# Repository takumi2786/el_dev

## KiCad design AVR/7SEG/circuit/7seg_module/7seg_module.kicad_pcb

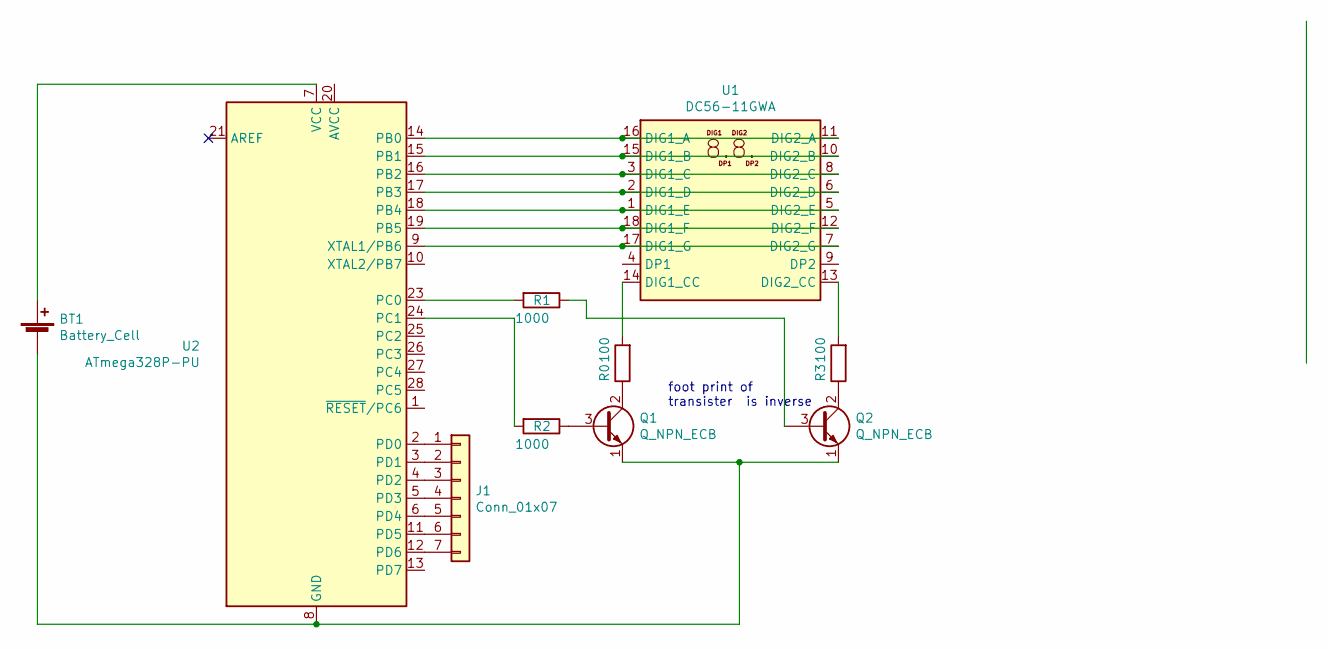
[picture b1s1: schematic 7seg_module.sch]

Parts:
BT1: Battery_Cell; v_dip
J1: Conn_01x07; PinSocket_1x07_P2.54mm_Horizontal
Q1: Q_NPN_ECB; TO-92L_Inline
Q2: Q_NPN_ECB; TO-92_Inline
R0, R3: 100; R_Axial_DIN0309_L9.0mm_D3.2mm_P12.70mm_Horizontal
R1, R2: 1000; R_Axial_DIN0309_L9.0mm_D3.2mm_P12.70mm_Horizontal
U1: DC56-11GWA; DA56-11CGKWA
U2: ATmega328P-PU; DIL28

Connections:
unnamed: BT1.1 (+), U2.7 (VCC)
unnamed: BT1.2 (-), Q1.1 (E), Q2.1 (E), U2.8 (GND), U2.22 (GND)
unnamed: J1.1, U2.2 (PD0)
unnamed: J1.2, U2.3 (PD1)
unnamed: J1.3, U2.4 (PD2)
unnamed: J1.4, U2.5 (PD3)
unnamed: J1.5, U2.6 (PD4)
unnamed: J1.6, U2.11 (PD5)
unnamed: J1.7, U2.12 (PD6)
unnamed: Q1.2 (C), R0.1
unnamed: Q1.3 (B), R2.1
unnamed: Q2.2 (C), R3.1
unnamed: Q2.3 (B), R1.1
unnamed: R0.2, U1.14 (DIG1_CC)
unnamed: R1.2, U2.23 (PC0)
unnamed: R2.2, U2.24 (PC1)
unnamed: R3.2, U1.13 (DIG2_CC)
unnamed: U1.1 (DIG1_E), U1.5 (DIG2_E), U2.18 (PB4)
unnamed: U1.2 (DIG1_D), U1.6 (DIG2_D), U2.17 (PB3)
unnamed: U1.3 (DIG1_C), U1.8 (DIG2_C), U2.16 (PB2)
unnamed: U1.10 (DIG2_B), U1.15 (DIG1_B), U2.15 (PB1)
unnamed: U1.11 (DIG2_A), U1.16 (DIG1_A), U2.14 (PB0)
unnamed: U1.12 (DIG2_F), U1.18 (DIG1_F), U2.19 (PB5)
unnamed: U1.7 (DIG2_G), U1.17 (DIG1_G), U2.9 (XTAL1/PB6)

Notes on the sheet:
foot print of transister is inverse

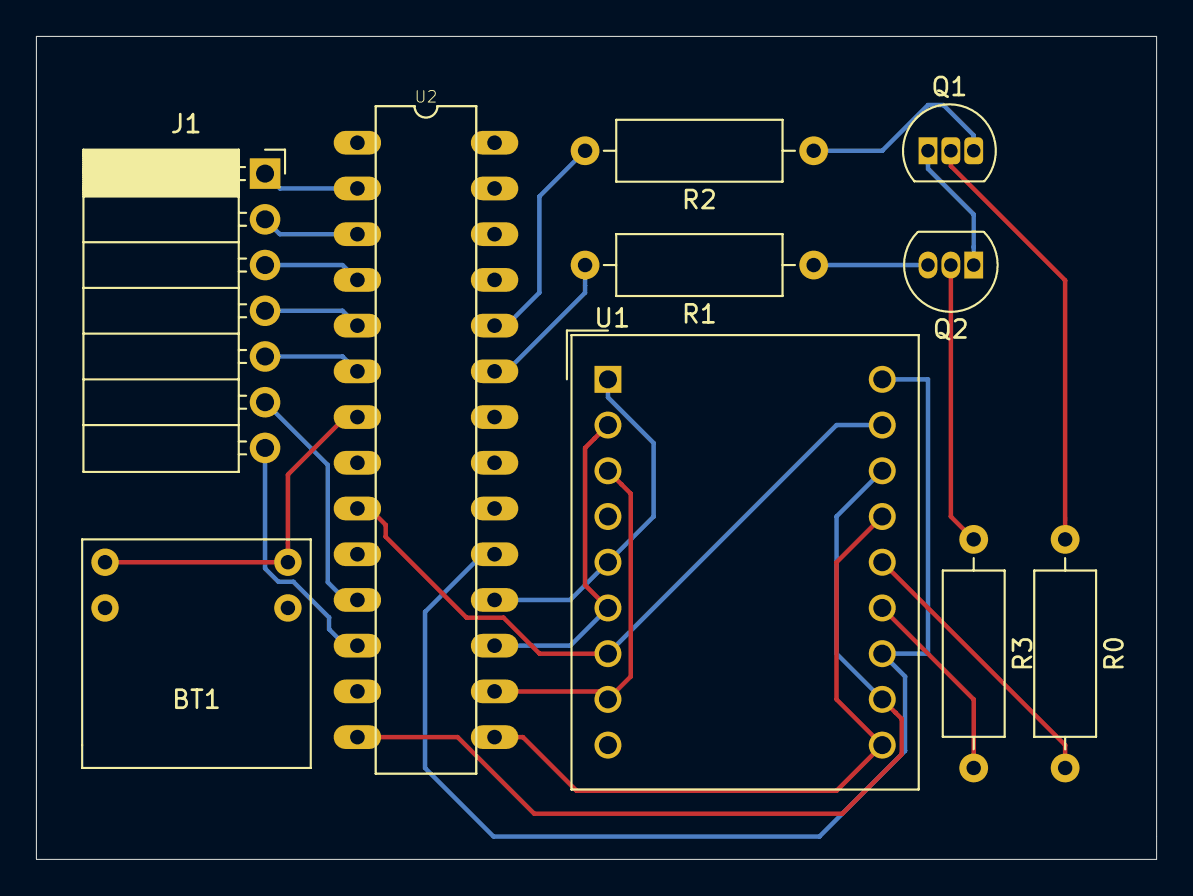
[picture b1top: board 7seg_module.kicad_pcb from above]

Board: 2 copper layers, 62.2 x 45.7 mm, 10 parts (0 on the bottom side), 24 nets.

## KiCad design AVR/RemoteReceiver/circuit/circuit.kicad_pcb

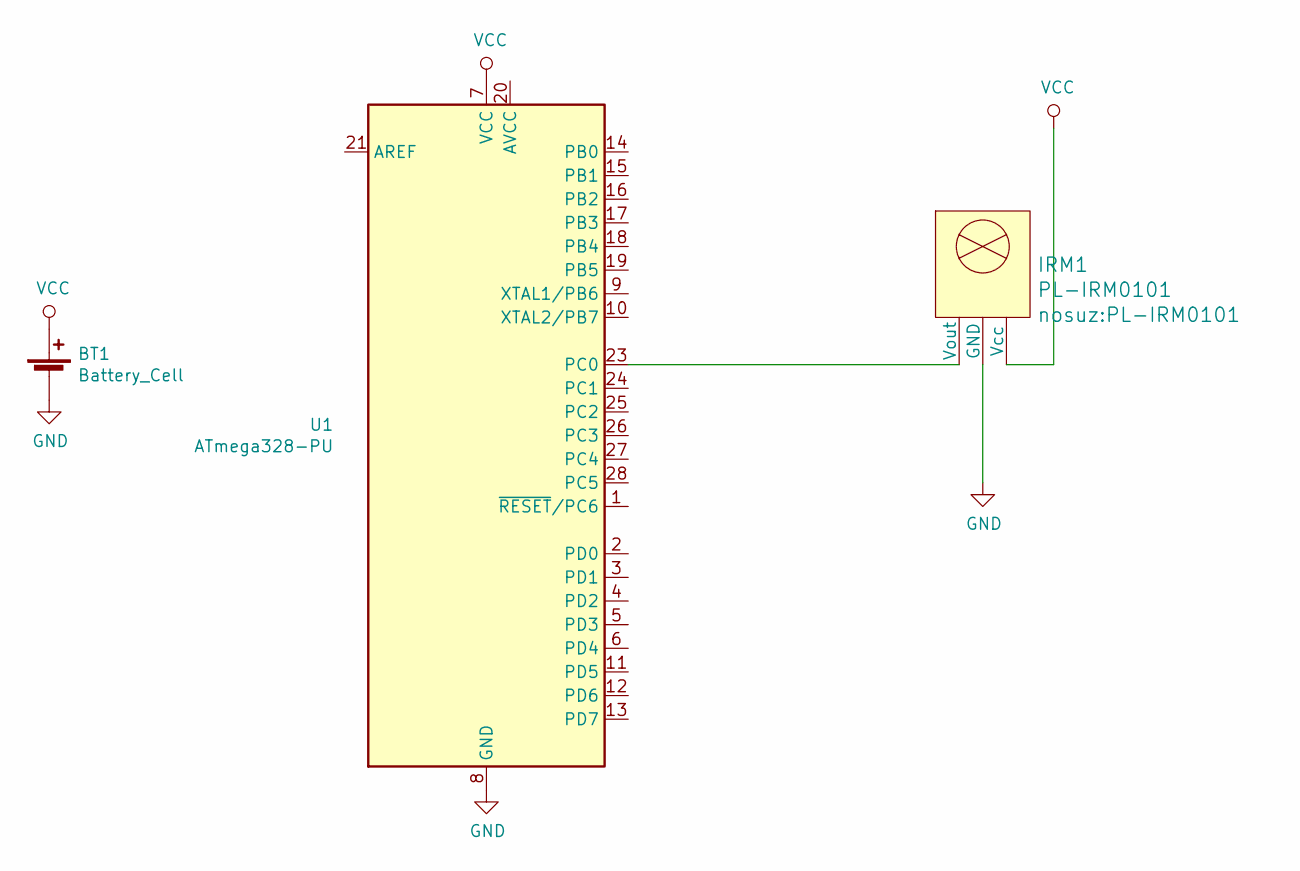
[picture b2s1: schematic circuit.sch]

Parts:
BT1: Battery_Cell; v_dip
IRM1: PL-IRM0101
U1: ATmega328-PU; DIP-28_W7.62mm

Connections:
GND: BT1.2 (-), IRM1.2 (GND), U1.8 (GND), U1.22 (GND)
unnamed: IRM1.1 (Vout), U1.23 (PC0)
VCC: BT1.1 (+), IRM1.3 (Vcc), U1.7 (VCC)

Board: 2 copper layers, 3 parts (0 on the bottom side), 3 nets, no tracks yet.

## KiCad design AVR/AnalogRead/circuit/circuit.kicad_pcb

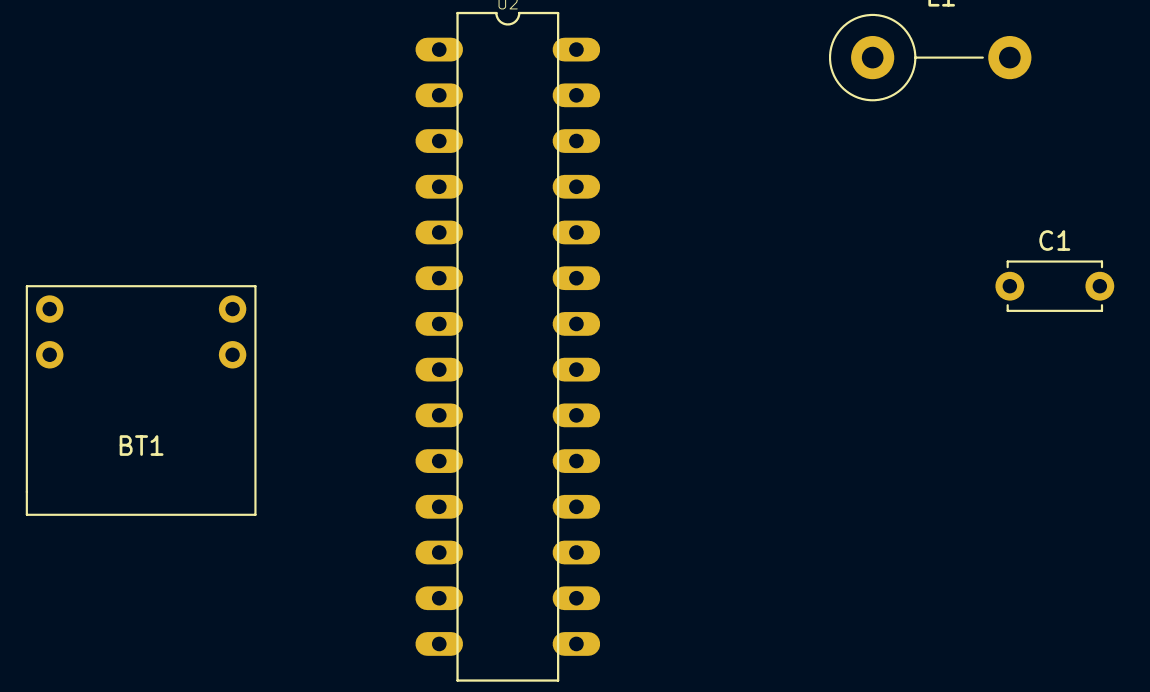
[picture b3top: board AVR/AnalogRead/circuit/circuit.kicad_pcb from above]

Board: 2 copper layers, 4 parts (0 on the bottom side), 3 nets, no tracks yet.

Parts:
BT1: Battery_Cell; v_dip
C1: 0.1u; C_Disc_D5.0mm_W2.5mm_P5.00mm
L1: 0.1u; L_Axial_L13.0mm_D4.5mm_P7.62mm_Vertical_Fastron_HCCC
U2: ATmega328P-PU; DIL28

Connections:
GND: BT1.2, C1.1, U2.8, U2.22
unnamed: C1.2, L1.2, U2.20
VCC: BT1.1, L1.1, U2.7

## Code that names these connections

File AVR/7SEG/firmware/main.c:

// 7SEG LED ATMEGA328puß用
// 二進数4桁で入力を受け取り，7seg LEDに出力する．

// これめっちゃ使える．
#define SBI(reg,bit) reg |= (1 << bit)
#define CBI(reg,bit) reg &= ~(1 << bit)

#include <avr/io.h>
#include <util/delay.h>
#include <avr/interrupt.h>

// 入力ピン
#define InputPin0 0 //PD0
#define InputPin1 1 //PD1
#define InputPin2 2 //PD2
#define InputPin3 3 //PD3
#define InputPin4 4 //PD4
#define InputPin5 5 //PD5
#define InputPin6 6 //PD6 
// #define InputPin7 7 //PD6 

// 7seg出力
#define OutPinA 0 //PB0
#define OutPinB 1 //PB1
#define OutPinC 2 //PB2
#define OutPinD 3 //PB3
#define OutPinE 4 //PB4
#define OutPinF 5 //PB5
#define OutPinG 6 //PB6

// 桁表示フラグ 出力
#define dig_out0 0 //PC0
#define dig_out1 1 //PC1

int get_number(){
	char N=0;

	// // int var=0;
	// // 一桁目取得
	// N = N | ( PIND & (0b01<<0));
	// // 二桁目取得
	// N = N | ( PIND & (0b01<<1));
	// bool bit;

	char temp = PIND;

	// bit反転
	temp = ~temp;
	CBI(temp,7);
	// 8bit目を強制的に0にする
	N=temp;

	return (int)N;
}

void disp_dig(int N,int dig){
	// digitの選択
	// 一旦全部消す
	
	CBI(PORTC, dig_out0);
	CBI(PORTC, dig_out1);
	PORTB=0;

	// 桁を表示
	switch(dig){
		case 0:
			SBI(PORTC, dig_out0);
			CBI(PORTC, dig_out1);
		break;
		case 1:
			CBI(PORTC, dig_out0);
			SBI(PORTC, dig_out1);
		break;
	}

	// 数字を出力
	switch (N){
	  case 0:
	    SBI(PORTB, OutPinA);
		SBI(PORTB, OutPinB);
		SBI(PORTB, OutPinC);
		SBI(PORTB, OutPinD);
		SBI(PORTB, OutPinE);
		SBI(PORTB, OutPinF);
		CBI(PORTB, OutPinG);
	  break;
	  case 1:
	    CBI(PORTB, OutPinA);
		SBI(PORTB, OutPinB);
		SBI(PORTB, OutPinC);
		CBI(PORTB, OutPinD);
		CBI(PORTB, OutPinE);
		CBI(PORTB, OutPinF);
		CBI(PORTB, OutPinG);
	  break;
	  case 2:
	    SBI(PORTB, OutPinA);
		SBI(PORTB, OutPinB);
		CBI(PORTB, OutPinC);
		SBI(PORTB, OutPinD);
		SBI(PORTB, OutPinE);
		CBI(PORTB, OutPinF);
		SBI(PORTB, OutPinG);

		// PORTB=0b1011011;
	  break;
	  case 3:
	    SBI(PORTB, OutPinA);
		SBI(PORTB, OutPinB);
		SBI(PORTB, OutPinC);
		SBI(PORTB, OutPinD);
		CBI(PORTB, OutPinE);
		CBI(PORTB, OutPinF);
		SBI(PORTB, OutPinG);
	  break;
	  case 4:
	    CBI(PORTB, OutPinA);
		SBI(PORTB, OutPinB);
		SBI(PORTB, OutPinC);
		CBI(PORTB, OutPinD);
		CBI(PORTB, OutPinE);
		SBI(PORTB, OutPinF);
		SBI(PORTB, OutPinG);
	  break;
	  case 5:
	    SBI(PORTB, OutPinA);
		CBI(PORTB, OutPinB);
		SBI(PORTB, OutPinC);
		SBI(PORTB, OutPinD);
		CBI(PORTB, OutPinE);
		SBI(PORTB, OutPinF);
		SBI(PORTB, OutPinG);
	  break;
	  case 6:
	    SBI(PORTB, OutPinA);
		CBI(PORTB, OutPinB);
		SBI(PORTB, OutPinC);
		SBI(PORTB, OutPinD);
		SBI(PORTB, OutPinE);
		SBI(PORTB, OutPinF);
		SBI(PORTB, OutPinG);
	  break;
	  case 7:
	    SBI(PORTB, OutPinA);
		SBI(PORTB, OutPinB);
		SBI(PORTB, OutPinC);
		CBI(PORTB, OutPinD);
		CBI(PORTB, OutPinE);
		SBI(PORTB, OutPinF);
		CBI(PORTB, OutPinG);

		// PORTB=0b0100111;

		break;
	  case 8:
	    SBI(PORTB, OutPinA);
		SBI(PORTB, OutPinB);
		SBI(PORTB, OutPinC);
		SBI(PORTB, OutPinD);
		SBI(PORTB, OutPinE);
		SBI(PORTB, OutPinF);
		SBI(PORTB, OutPinG);
		break;
	  case 9:
	    SBI(PORTB, OutPinA);
		SBI(PORTB, OutPinB);
		SBI(PORTB, OutPinC);
		SBI(PORTB, OutPinD);
		CBI(PORTB, OutPinE);
		SBI(PORTB, OutPinF);
		SBI(PORTB, OutPinG);
		break;
	}
	
}


void disp_numbers(int N){
	int N_1, N_10;
	// 1の位を取得
	N_1 = N % 10;

	// 10の位を取得
	N=N/10;
	N_10 = N % 10;

	disp_dig(N_1,0);
	disp_dig(N_10,1);

}

void init(){
	// PIN設定
	// 入力ピン
	CBI(DDRD, InputPin0);
	CBI(DDRD, InputPin1);
	CBI(DDRD, InputPin2);
	CBI(DDRD, InputPin3);
	CBI(DDRD, InputPin4);
	CBI(DDRD, InputPin5);
	CBI(DDRD, InputPin6);
	// CBI(DDRD, InputPin7);

	// プルアップ
	SBI(PORTD, InputPin0);
	SBI(PORTD, InputPin1);
	SBI(PORTD, InputPin2);
	SBI(PORTD, InputPin3);
	SBI(PORTD, InputPin4);
	SBI(PORTD, InputPin5);
	SBI(PORTD, InputPin6);
	// SBI(PORTD, InputPin7);

	// 一桁目
	SBI(DDRB, OutPinA);
	SBI(DDRB, OutPinB);
	SBI(DDRB, OutPinC);
	SBI(DDRB, OutPinD);
	SBI(DDRB, OutPinE);
	SBI(DDRB, OutPinF);
	SBI(DDRB, OutPinG);

	// 出力する桁を選択するピン
	SBI(DDRC, dig_out0);

	SBI(DDRC, dig_out1);
	
}

int main(){
	init();
	int N=0;
	while(1){
		// 入力値を取得
		N = get_number();
		// 数字を出力
		disp_numbers(N);
		// for (int i = 0; i < 100; ++i){
			
			// _delay_ms(1000);
		// }
		// disp_number(88);
	}
	
	
	// SBI(PORTB, OutPinA);
	// SBI(PORTB, OutPinB);
	// SBI(PORTB, OutPinC);
	// SBI(PORTB, OutPinD);
	// SBI(PORTB, OutPinE);
	// SBI(PORTB, OutPinF);
	// SBI(PORTB, OutPinG);


	return 0;
}

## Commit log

2021-01-23 整理整頓
2021-01-23 回路はやっぱり入れたほうが良い
